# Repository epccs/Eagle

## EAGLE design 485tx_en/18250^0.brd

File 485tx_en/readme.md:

[485tx_en]

RS485 txcvr with fail-safe (e.g. 0V on A/B give HIGH on RO), thus TX can be used to enable media (A/B pair) driver. It does not work with industary standard based equipment.

[485tx_en]: https://github.com/epccs/Driver/tree/master/485tx_en

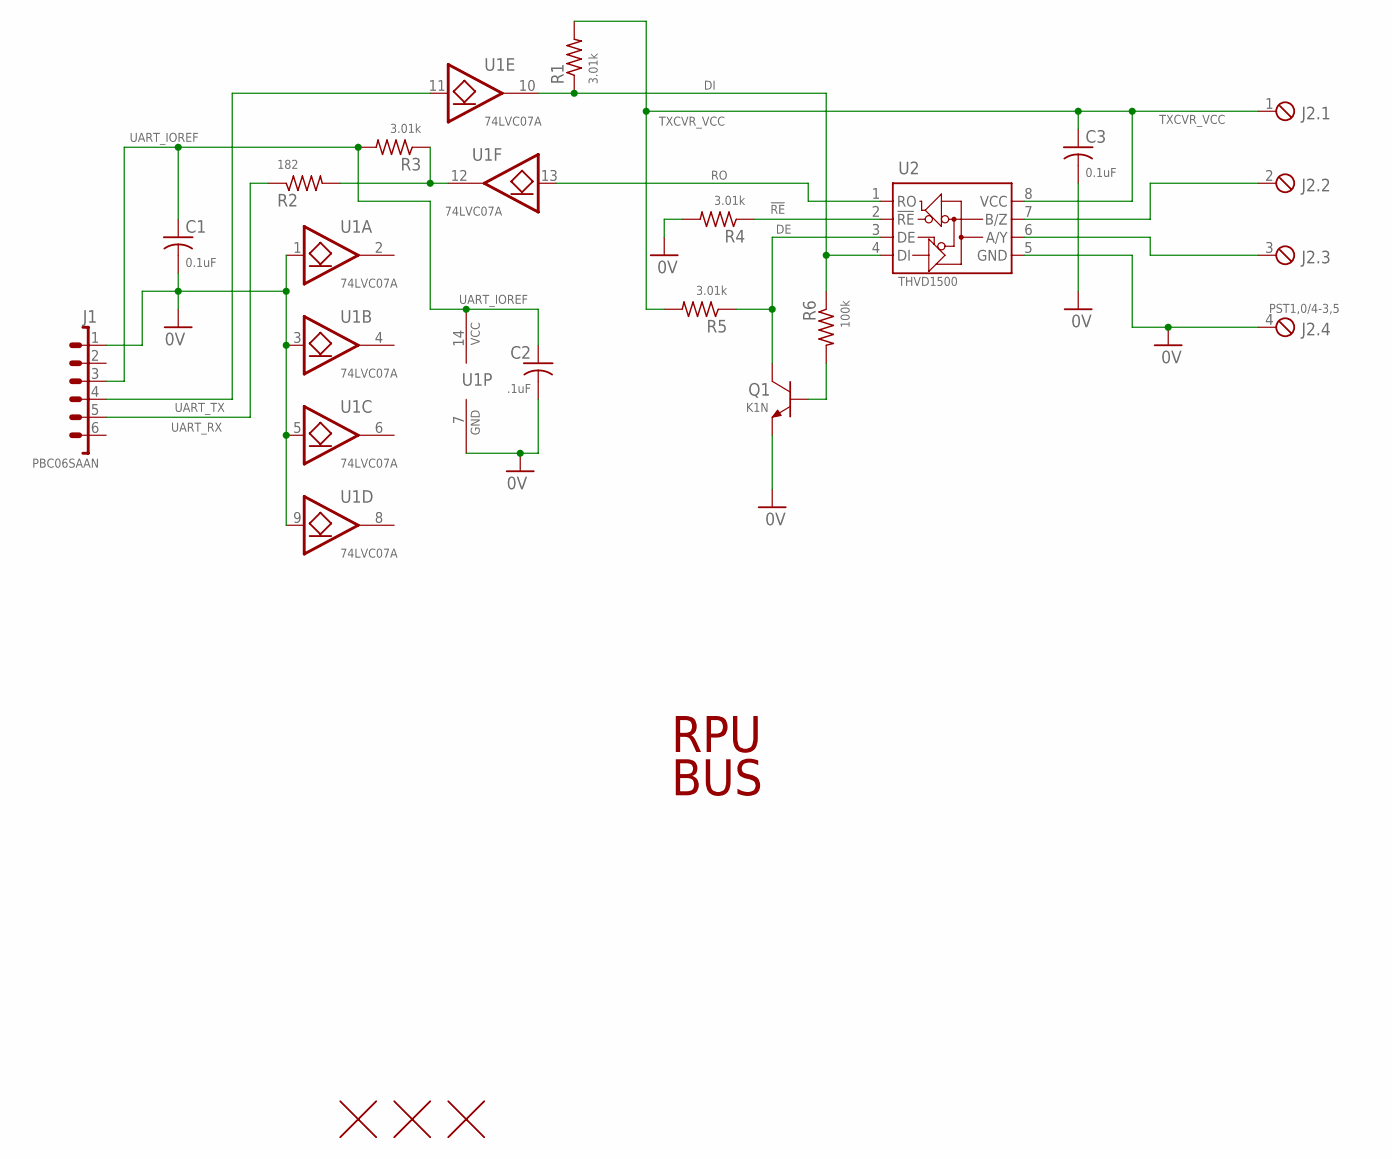
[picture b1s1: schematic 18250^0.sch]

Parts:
C1, C3: 0.1uF; C0603(1608)
C2: .1uF; C0603(1608)
J1: PBC06SAAN; 1X6
J2: PST1,0/4-3,5; MCV4
Q1: K1N; SOT23
R1, R3, R4, R5: 3.01k; C0805(2012)
R2: 182; C0805(2012)
R6: 100k; C0805(2012)
U1: 74LVC07A; 14SOIC
U2: THVD1500; SOIC8
U$2, U$3, U$4: FIDUCIAL1.27; FIDUCIAL-1.27

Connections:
0V: C1.2, C2.2, C3.2, J1.1, J2.4, Q1.E, R4.2, U1.1 (I), U1.3 (I), U1.5 (I), U1.7 (GND), U1.9 (I), U2.5 (GND)
!RE: R4.1, U2.2 (!RE)
A: J2.3, U2.6 (A/Y)
B: J2.2, U2.7 (B/Z)
DE: Q1.C, R5.1, U2.3 (DE)
DI: R1.1, R6.1, U1.10 (O), U2.4 (DI)
unnamed: R2.2, R3.1, U1.12 (O)
unnamed: Q1.B, R6.2
RO: U1.13 (I), U2.1 (RO)
TXCVR_VCC: C3.1, J2.1, R1.2, R5.2, U2.8 (VCC)
UART_IOREF: C1.1, C2.1, J1.3, R3.2, U1.14 (VCC)
UART_RX: J1.5, R2.1
UART_TX: J1.4, U1.11 (I)

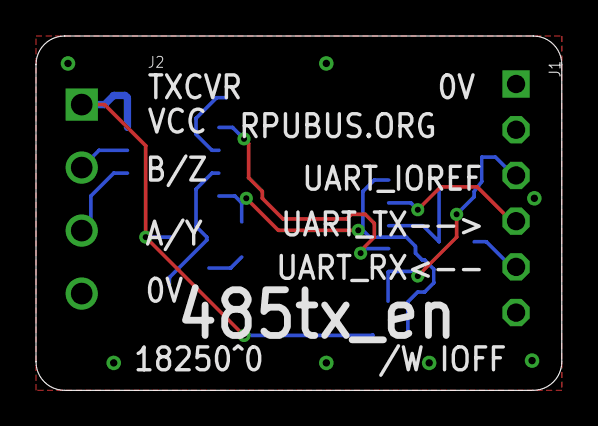
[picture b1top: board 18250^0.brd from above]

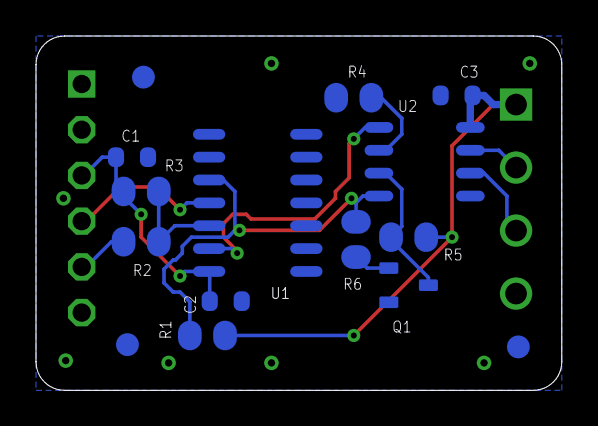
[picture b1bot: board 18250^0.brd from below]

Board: 2 copper layers, 29.2 x 19.7 mm, 17 parts (15 on the bottom side), 13 nets.

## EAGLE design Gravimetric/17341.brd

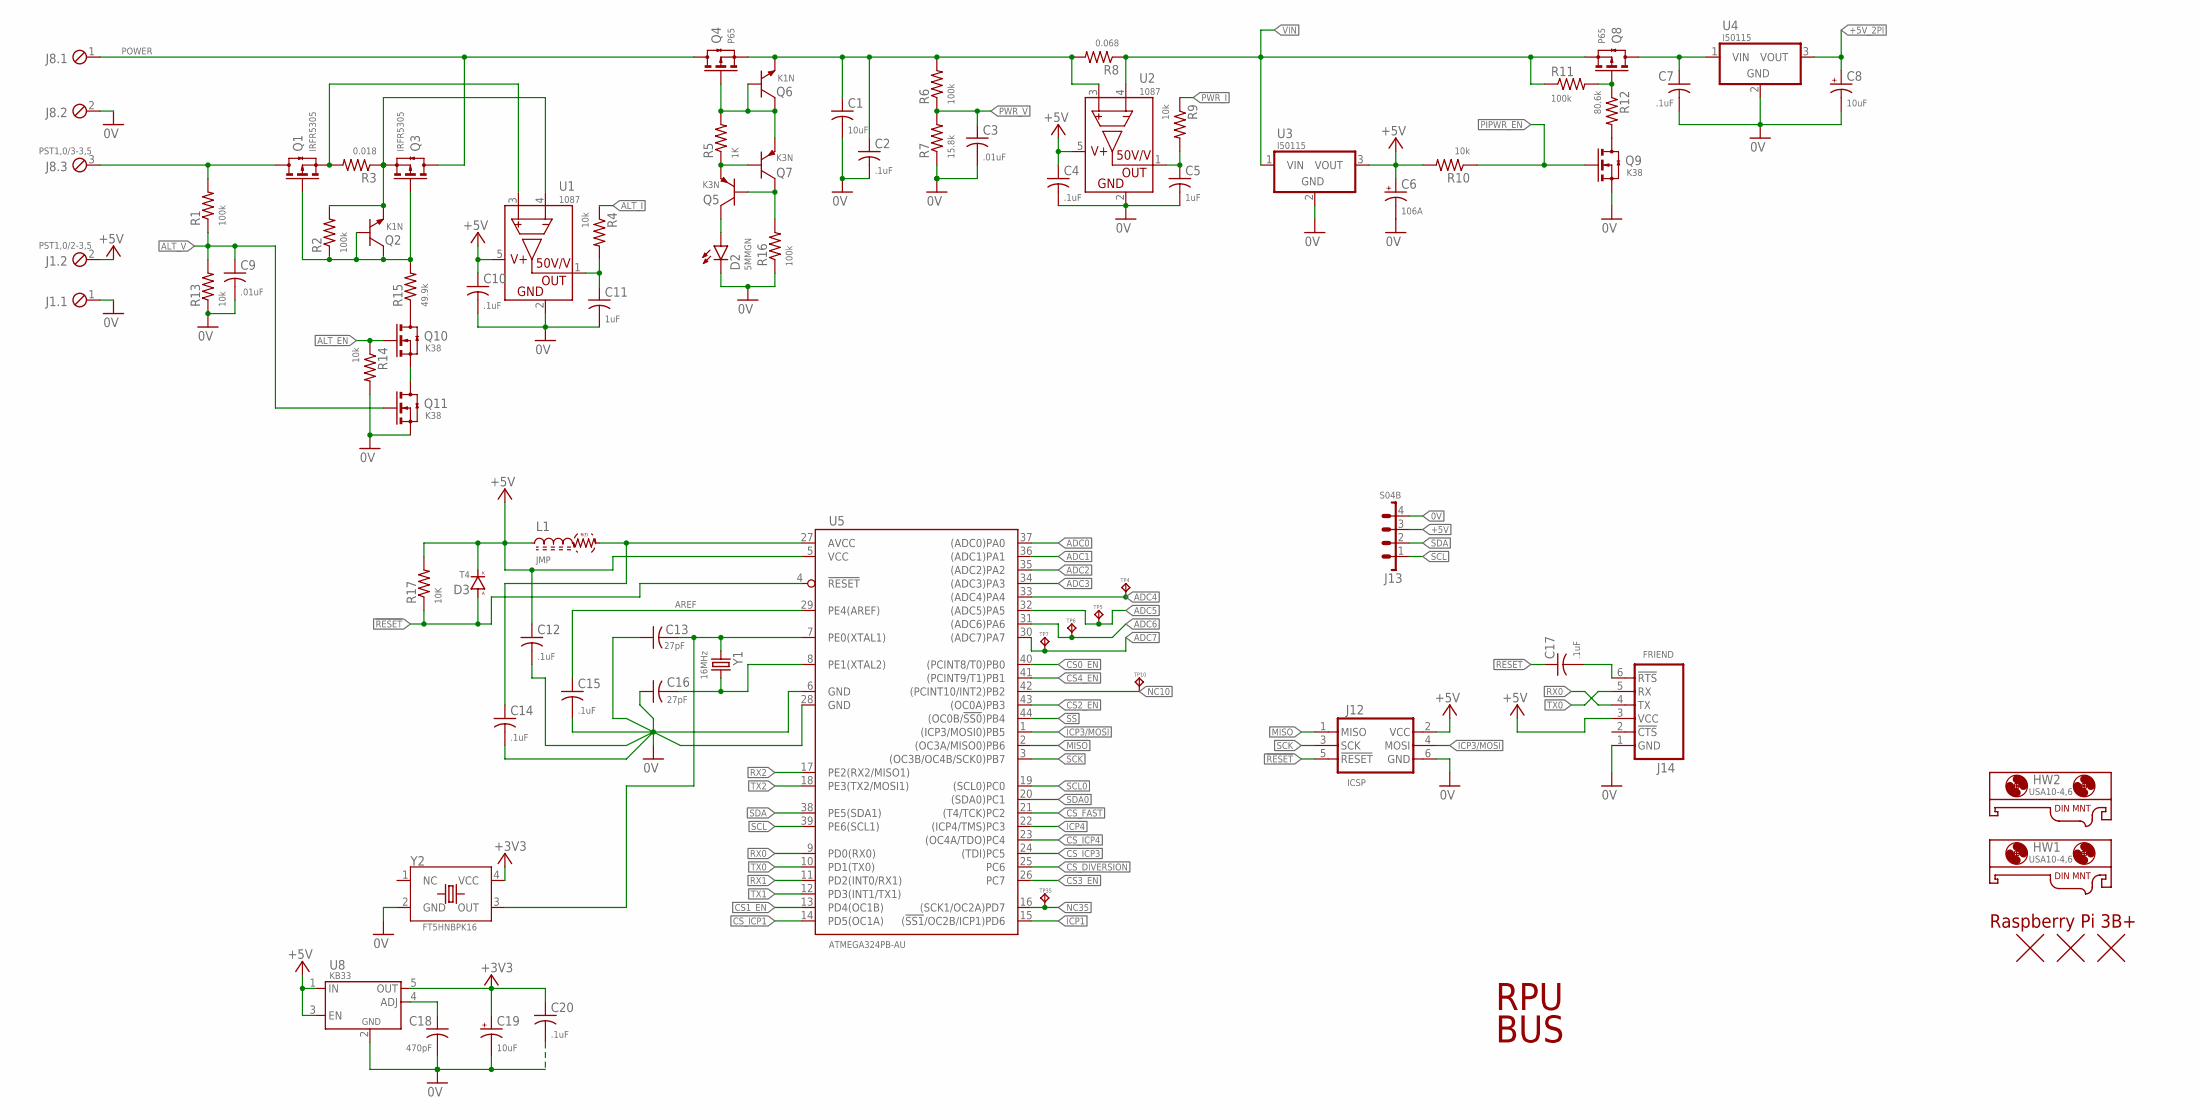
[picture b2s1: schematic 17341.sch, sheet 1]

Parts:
C1: 10uF; C1206(3216)
C2: .1uF; C0805(2012)
C3, C9: .01uF; C0603(1608)
C4, C7, C10, C12, C14, C15, C17, C20: .1uF; C0603(1608)
C5, C11: 1uF; C0805(2012)
C6: 106A; 3216
C8, C19: 10uF; 3216
C13, C16: 27pF; C0603(1608)
C18: 470pF; C0603(1608)
D2: 5MMGN; LED5MM
D3: T4; SOD123
HW1, HW2: USA10-4,6; USA10
J1: PST1,0/2-3,5; MCV2
J8: PST1,0/3-3,5; MCV3
J12: ICSP; ISP
J13: S04B; B04B
J14: FRIEND
L1: JMP; C0805(2012)
Q1, Q3: IRFR5305; DPAK
Q2, Q6: K1N; SOT23
Q4, Q8: P65; SOT23
Q5, Q7: K3N; SOT23
Q9, Q10, Q11: K38; SOT23
R1, R2, R6, R11, R16: 100k; C0805(2012)
R3: 0.018; C1210(3225)
R4, R9, R10, R13, R14: 10k; C0805(2012)
R5: 1K; C0805(2012)
R7: 15.8k; C0805(2012)
R8: 0.068; C1210(3225)
R12: 80.6k; C0805(2012)
R15: 49.9k; C0805(2012)
R17: 10K; C0805(2012)
TP4, TP5, TP6, TP7, TP10, TP35: TPPAD1-08; P1-08
U1, U2: 1087; SOT23-5
U3, U4: I50115; OKI-78SR-H
U5: ATMEGA324PB-AU; TQFP44
U8: KB33; SOT23-5,SOT25
U$1: R-PI3B+
U$2, U$3, U$4: FIDUCIAL1.27; FIDUCIAL-1.27
Y1: 16MHz; CSM-3X
Y2: FT5HNBPK16; CRYSTAL5X3.2MM

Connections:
0V: C1.2, C2.2, C3.2, C4.2, C5.2, C6.-, C7.2, C8.-, C9.2, C10.2, C11.2, C12.2, C13.1, C14.2, C15.2, C16.1, C18.2, C19.-, C20.2, D2.K, J1.1, J8.2, J12.6 (GND), J13.4, J14.1 (GND), Q9.2(S) (S), Q11.2(S) (S), R7.1, R13.1, R14.2, R16.1, U1.2 (GND), U2.2 (GND), U3.2 (GND), U4.2 (GND), U5.6 (GND), U5.28 (GND), U8.2 (GND), Y2.2 (GND); also elsewhere on the board
!RESET!: C17.1, D3.A, J12.5 (!RESET), R17.1, U5.4 (!RESET); also elsewhere on the board
!SS: U5.44 ((OC0B/!SS0!)PB4); also elsewhere on the board
+3V3: C19.+, C20.1, U8.5 (OUT), Y2.4 (VCC)
+5V: C4.1, C6.+, C10.1, C12.1, D3.C (K), J1.2, J12.2 (VCC), J13.3, J14.3 (VCC), L1.1, R10.2, R17.2, U1.5 (VCC), U2.5 (VCC), U3.3 (VOUT), U5.5 (VCC), U8.1 (IN), U8.3 (EN); also elsewhere on the board
+5V_2PI: C8.+, U4.3 (VOUT); also elsewhere on the board
ADC0: U5.37 ((ADC0)PA0); also elsewhere on the board
ADC1: U5.36 ((ADC1)PA1); also elsewhere on the board
ADC2: U5.35 ((ADC2)PA2); also elsewhere on the board
ADC3: U5.34 ((ADC3)PA3); also elsewhere on the board
ADC4: TP4.TP, U5.33 ((ADC4)PA4)
ADC5: TP5.TP, U5.32 ((ADC5)PA5)
ADC6: TP6.TP, U5.31 ((ADC6)PA6)
ADC7: TP7.TP, U5.30 ((ADC7)PA7)
ALT_EN: Q10.1(G) (G), R14.1; also elsewhere on the board
ALT_I: R4.1; also elsewhere on the board
ALT_V: C9.1, Q11.1(G) (G), R1.1, R13.2; also elsewhere on the board
AREF: C15.1, U5.29 (PE4(AREF))
CS0_EN: U5.40 ((PCINT8/T0)PB0); also elsewhere on the board
CS1_EN: U5.13 (PD4(OC1B)); also elsewhere on the board
CS2_EN: U5.43 ((OC0A)PB3); also elsewhere on the board
CS3_EN: U5.26 (PC7); also elsewhere on the board
CS4_EN: U5.41 ((PCINT9/T1)PB1); also elsewhere on the board
CS_DIVERSION: U5.25 (PC6); also elsewhere on the board
CS_FAST: U5.21 ((T4/TCK)PC2); also elsewhere on the board
CS_ICP1: U5.14 (PD5(OC1A)); also elsewhere on the board
CS_ICP3: U5.24 ((TDI)PC5); also elsewhere on the board
CS_ICP4: U5.23 ((OC4A/TDO)PC4); also elsewhere on the board
ICP1: U5.15 ((!SS1!/OC2B/ICP1)PD6); also elsewhere on the board
ICP3/MOSI: J12.4 (MOSI), U5.1 ((ICP3/MOSI0)PB5); also elsewhere on the board
ICP4: U5.22 ((ICP4/TMS)PC3); also elsewhere on the board
MISO: J12.1 (MISO), U5.2 ((OC3A/MISO0)PB6); also elsewhere on the board
unnamed: Q8.1(G) (G), R11.2, R12.1
unnamed: Q9.3(D) (D), R12.2
unnamed: Q5.B, Q7.C, R16.2
unnamed: Q4.1(G) (G), Q6.B, Q6.C, Q7.E, R5.2
unnamed: D2.A, Q5.C
unnamed: C5.1, R9.2, U2.1 (OUT)
unnamed: Q5.E, Q7.B, R5.1
unnamed: J8.3, Q1.SINK (D), R1.2
unnamed: Q2.E, Q3.3 (S), R2.2, R3.1, U1.4 (S-)
unnamed: Q1.1 (G), Q2.B, Q2.C, Q3.1 (G), R2.1, R15.2
unnamed: Q10.3(D) (D), R15.1
unnamed: C17.2, J14.6 (!RTS)
unnamed: C11.1, R4.2, U1.1 (OUT)
unnamed: Q1.3 (S), R3.2, U1.3 (S+)
unnamed: C16.2, U5.8 (PE1(XTAL2)), Y1.2
unnamed: C18.1, U8.4 (ADJ)
unnamed: C14.1, L1.2, U5.27 (AVCC)
unnamed: C13.2, U5.7 (PE0(XTAL1)), Y1.1, Y2.3 (OUT)
unnamed: Q10.2(S) (S), Q11.3(D) (D)
NC10: TP10.TP, U5.42 ((PCINT10/INT2)PB2)
NC35: TP35.TP, U5.16 ((SCK1/OC2A)PD7)
PIPWR_EN: Q9.1(G) (G), R10.1; also elsewhere on the board
POWER: J8.1, Q3.SINK (D), Q4.3(D) (D)
PWR_I: R9.1; also elsewhere on the board
PWR_V: C3.1, R6.1, R7.2; also elsewhere on the board
RX0: J14.4 (TX), U5.9 (PD0(RX0)); also elsewhere on the board
RX1: U5.11 (PD2(INT0/RX1)); also elsewhere on the board
RX2: U5.17 (PE2(RX2/MISO1)); also elsewhere on the board
SCK: J12.3 (SCK), U5.3 ((OC3B/OC4B/SCK0)PB7); also elsewhere on the board
SCL: J13.1, U5.39 (PE6(SCL1))
SCL0: U5.19 ((SCL0)PC0); also elsewhere on the board
SDA: J13.2, U5.38 (PE5(SDA1))
SDA0: U5.20 ((SDA0)PC1); also elsewhere on the board
SHLD_VIN: C7.1, Q8.3(D) (D), U4.1 (VIN)
TX0: J14.5 (RX), U5.10 (PD1(TX0)); also elsewhere on the board
TX1: U5.12 (PD3(INT1/TX1)); also elsewhere on the board
TX2: U5.18 (PE3(TX2/MOSI1)); also elsewhere on the board
VIN: Q8.2(S) (S), R8.1, R11.1, U2.4 (S-), U3.1 (VIN); also elsewhere on the board
VIN_S: C1.1, C2.1, Q4.2(S) (S), Q6.E, R6.2, R8.2, U2.3 (S+)

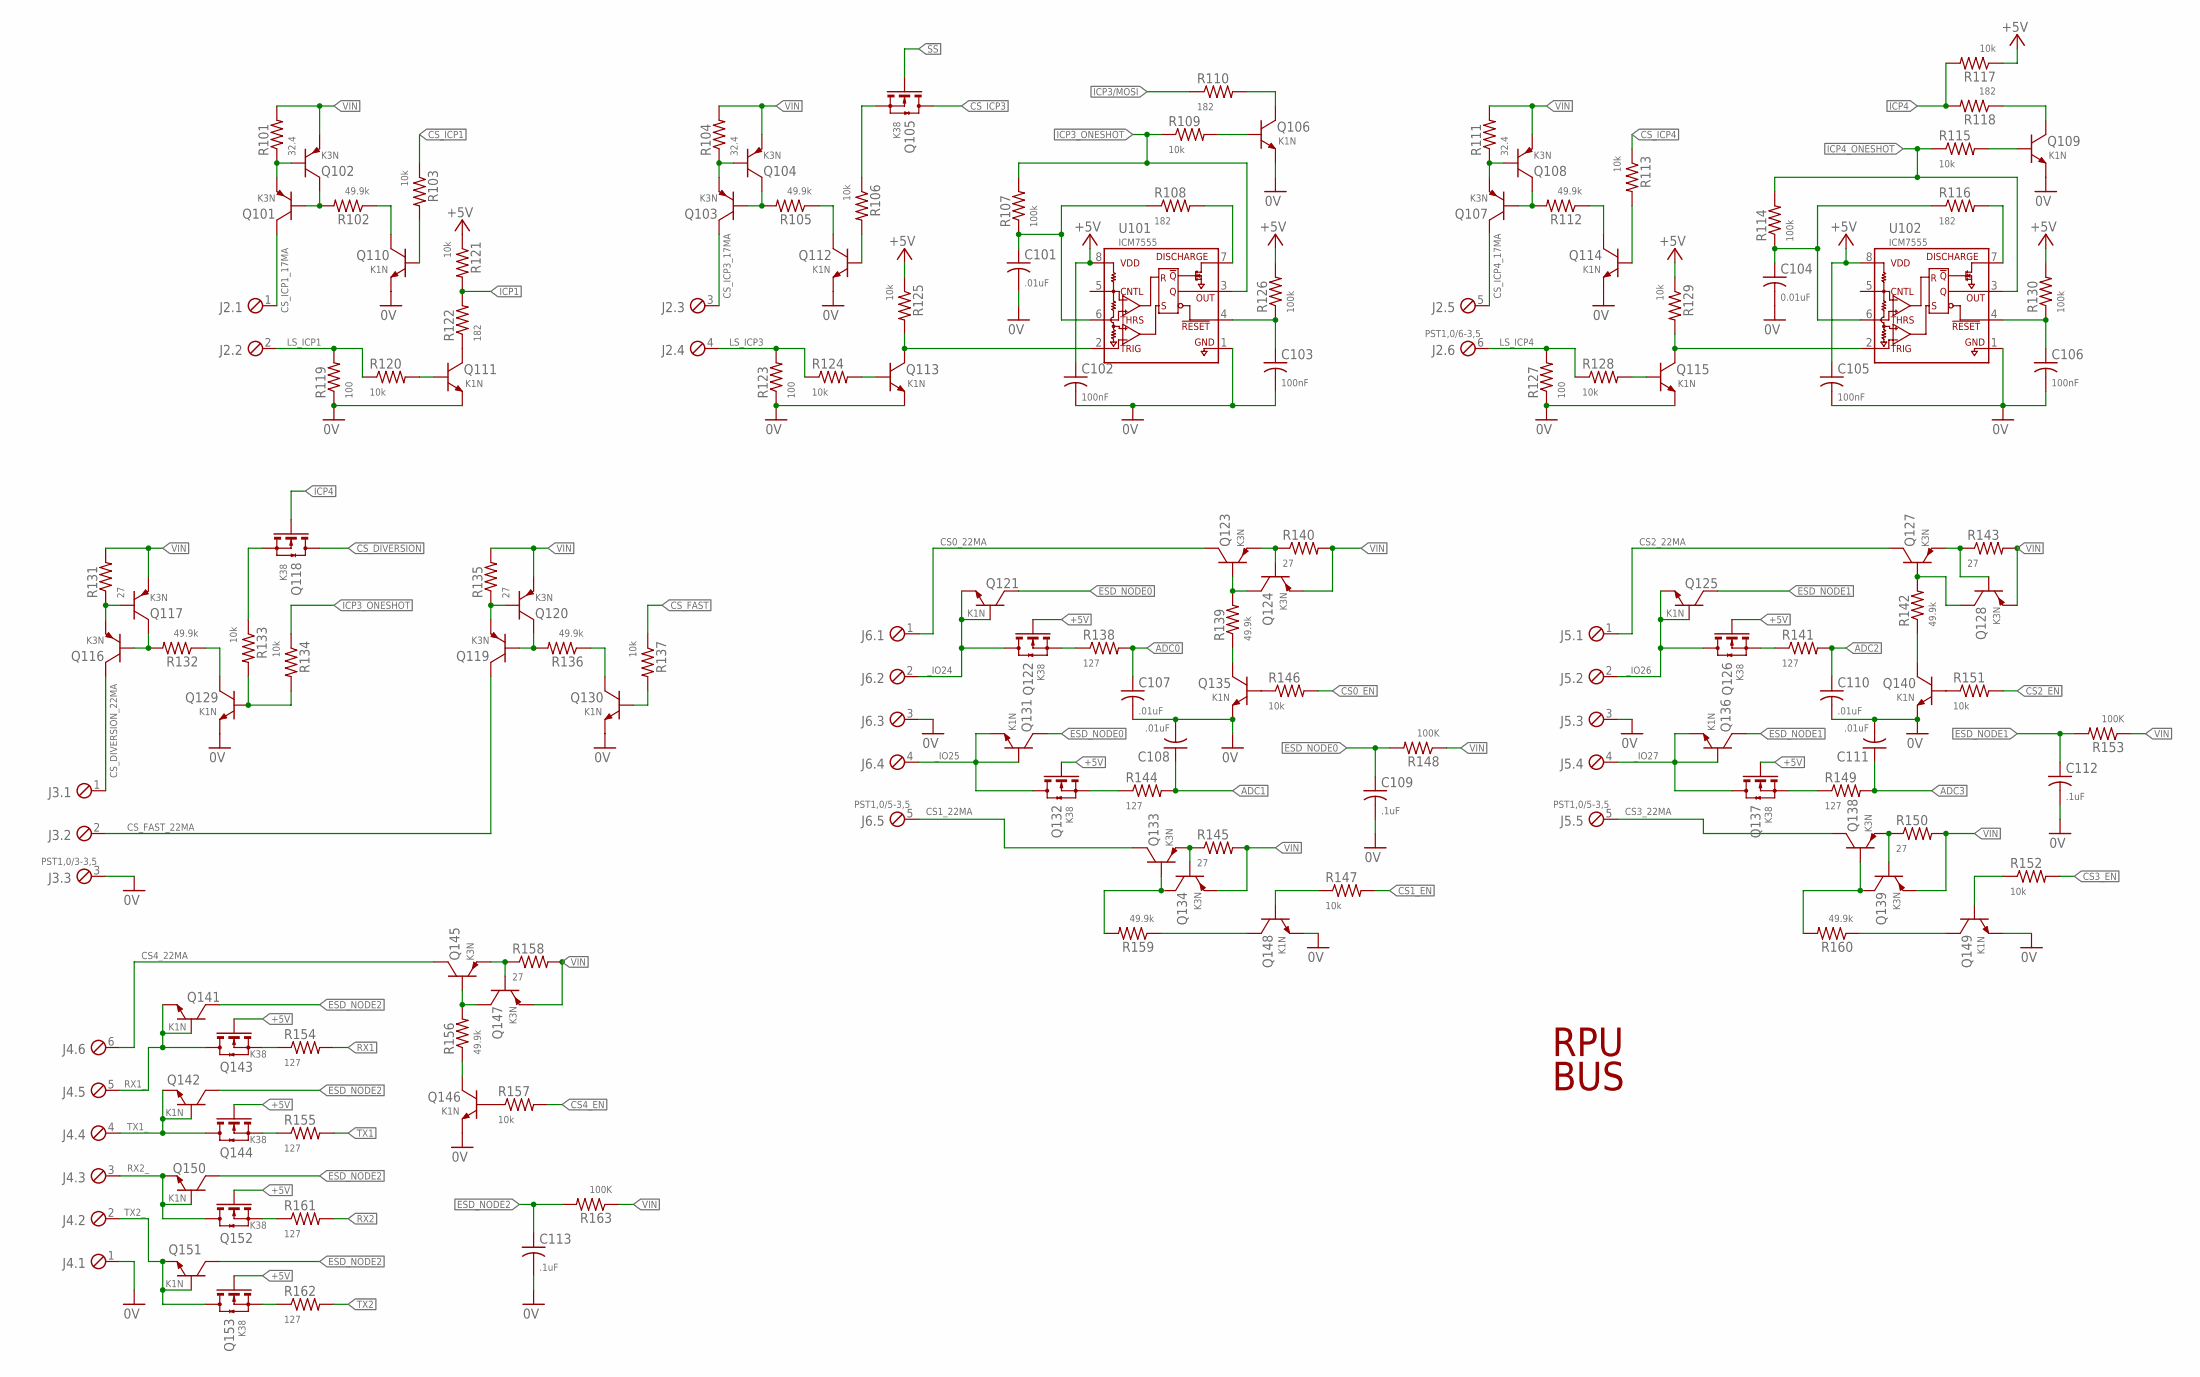
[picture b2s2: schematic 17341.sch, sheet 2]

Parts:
C101: .01uF; C0805(2012)
C102, C103, C105, C106: 100nF; C0603(1608)
C104: 0.01uF; C0805(2012)
C107, C108, C110, C111: .01uF; C0603(1608)
C109, C112, C113: .1uF; C0603(1608)
J2: PST1,0/6-3,5; MCV6
J3: PST1,0/3-3,5; MCV3
J4: MCV6
J5, J6: PST1,0/5-3,5; MCV5
Q101, Q102, Q103, Q104, Q107, Q108, Q116, Q117, Q119, Q120, Q123, Q124, Q127, Q128, Q133, Q134, Q138, Q139, Q145, Q147: K3N; SOT23
Q105, Q118, Q122, Q126, Q132, Q137, Q143, Q144, Q152, Q153: K38; SOT23
Q106, Q109, Q110, Q111, Q112, Q113, Q114, Q115, Q121, Q125, Q129, Q130, Q131, Q135, Q136, Q140, Q141, Q142, Q146, Q148, Q149, Q150, Q151: K1N; SOT23
R101, R104, R111: 32.4; C0805(2012)
R102, R105, R112, R132, R136, R139, R142, R156, R159, R160: 49.9k; C0805(2012)
R103, R106, R109, R113, R115, R117, R120, R121, R124, R125, R128, R129, R133, R134, R137, R146, R147, R151, R152, R157: 10k; C0805(2012)
R107, R114, R126, R130: 100k; C0805(2012)
R108, R110, R116, R118, R122: 182; C0805(2012)
R119, R123, R127: 100; C0805(2012)
R131, R135, R140, R143, R145, R150, R158: 27; C0805(2012)
R138, R141, R144, R149, R154, R155, R161, R162: 127; C0805(2012)
R148, R153, R163: 100K; C0805(2012)
U101, U102: ICM7555; SOIC8

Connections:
0V: C101.2, C102.2, C103.2, C104.2, C105.2, C106.2, C107.2, C108.2, C109.2, C110.2, C111.2, C112.2, C113.2, J3.3, J4.1, J5.3, J6.3, Q106.E, Q109.E, Q110.E, Q111.E, Q112.E, Q113.E, Q114.E, Q115.E, Q129.E, Q130.E, Q135.E, Q140.E, Q146.E, Q148.E, Q149.E, R119.1, R123.1, R127.1, U101.1 (GND), U102.1 (GND); also elsewhere on the board
!SS: Q105.1(G) (G); also elsewhere on the board
+5V: C102.1, C105.1, Q122.1(G) (G), Q126.1(G) (G), Q132.1(G) (G), Q137.1(G) (G), Q143.1(G) (G), Q144.1(G) (G), Q152.1(G) (G), Q153.1(G) (G), R117.1, R121.1, R125.1, R126.2, R129.1, R130.2, U101.8 (VDD), U102.8 (VDD); also elsewhere on the board
ADC0: C107.1, R138.2; also elsewhere on the board
ADC1: C108.1, R144.2; also elsewhere on the board
ADC2: C110.1, R141.2; also elsewhere on the board
ADC3: C111.1, R149.2; also elsewhere on the board
CS0_22MA: J6.1, Q123.C
CS0_EN: R146.2; also elsewhere on the board
CS1_22MA: J6.5, Q133.C
CS1_EN: R147.2; also elsewhere on the board
CS2_22MA: J5.1, Q127.C
CS2_EN: R151.2; also elsewhere on the board
CS3_22MA: J5.5, Q138.C
CS3_EN: R152.2; also elsewhere on the board
CS4_22MA: J4.6, Q145.C
CS4_EN: R157.2; also elsewhere on the board
CS_DIVERSION: Q118.3(D) (D); also elsewhere on the board
CS_DIVERSION_22MA: J3.1, Q116.C
CS_FAST: R137.1; also elsewhere on the board
CS_FAST_22MA: J3.2, Q119.C
CS_ICP1: R103.1; also elsewhere on the board
CS_ICP1_17MA: J2.1, Q101.C
CS_ICP3: Q105.3(D) (D); also elsewhere on the board
CS_ICP3_17MA: J2.3, Q103.C
CS_ICP4: R113.1; also elsewhere on the board
CS_ICP4_17MA: J2.5, Q107.C
ESD_NODE0: C109.1, Q121.C, Q131.C, R148.2
ESD_NODE1: C112.1, Q125.C, Q136.C, R153.2
ESD_NODE2: C113.1, Q141.C, Q142.C, Q150.C, Q151.C, R163.2
ICP1: R121.2, R122.2; also elsewhere on the board
ICP1__: Q111.B, R120.2
ICP3/MOSI: R110.1; also elsewhere on the board
ICP3_ONESHOT: R107.2, R109.1, R134.1, U101.3 (OUT)
ICP3_TIMING_RAMP: C101.1, R107.1, R108.1, U101.6 (THRS)
ICP3__: Q113.B, R124.2
ICP4: Q118.1(G) (G), R117.2, R118.2; also elsewhere on the board
ICP4_ONESHOT: R114.2, R115.1, U102.3 (OUT)
ICP4_TIMING_RAMP: C104.1, R114.1, R116.1, U102.6 (THRS)
ICP4__: Q115.B, R128.2
LS_ICP1: J2.2, R119.2, R120.1
LS_ICP3: J2.4, R123.2, R124.1
LS_ICP4: J2.6, R127.2, R128.1
unnamed: Q127.E, Q128.B, R143.1
unnamed: Q110.B, R103.2
unnamed: Q127.B, Q128.C, R142.2
unnamed: Q103.E, Q104.B, R104.1
unnamed: Q138.E, Q139.B, R150.1
unnamed: Q132.2(S) (S), R144.1
unnamed: Q122.2(S) (S), R138.1
unnamed: Q138.B, Q139.C, R160.2
unnamed: Q103.B, Q104.C, R105.2
unnamed: Q115.C, R129.2, U102.2 (TRIG)
unnamed: Q148.C, R159.1
unnamed: Q123.E, Q124.B, R140.1
unnamed: Q135.C, R139.1
unnamed: Q112.B, R106.2
unnamed: Q123.B, Q124.C, R139.2
unnamed: Q107.E, Q108.B, R111.1
unnamed: Q107.B, Q108.C, R112.2
unnamed: Q109.B, R115.2
unnamed: Q133.E, Q134.B, R145.1
unnamed: Q133.B, Q134.C, R159.2
unnamed: Q114.B, R113.2
unnamed: Q148.B, R147.1
unnamed: Q135.B, R146.1
unnamed: Q149.C, R160.1
unnamed: Q110.C, R102.1
unnamed: Q112.C, R105.1
unnamed: Q114.C, R112.1
unnamed: Q105.2(S) (S), R106.1
unnamed: Q113.C, R125.2, U101.2 (TRIG)
unnamed: Q109.C, R118.1
unnamed: Q116.E, Q117.B, R131.1
unnamed: R116.2, U102.7 (DISCHARGE)
unnamed: C106.1, R130.1, U102.4 (!RESET)
unnamed: Q106.B, R109.2
unnamed: R108.2, U101.7 (DISCHARGE)
unnamed: Q106.C, R110.2
unnamed: C103.1, R126.1, U101.4 (!RESET)
unnamed: Q116.B, Q117.C, R132.2
unnamed: Q129.B, R133.2, R134.2
unnamed: Q129.C, R132.1
unnamed: Q118.2(S) (S), R133.1
unnamed: Q119.E, Q120.B, R135.1
unnamed: Q119.B, Q120.C, R136.2
unnamed: Q130.B, R137.2
unnamed: Q130.C, R136.1
unnamed: Q140.C, R142.1
unnamed: Q137.2(S) (S), R149.1
unnamed: Q126.2(S) (S), R141.1
unnamed: Q149.B, R152.1
unnamed: Q140.B, R151.1
unnamed: Q145.E, Q147.B, R158.1
unnamed: Q145.B, Q147.C, R156.2
unnamed: Q153.2(S) (S), R162.1
unnamed: Q152.2(S) (S), R161.1
unnamed: Q146.C, R156.1
unnamed: Q144.2(S) (S), R155.1
unnamed: Q143.2(S) (S), R154.1
unnamed: Q146.B, R157.1
unnamed: Q111.C, R122.1
unnamed: Q101.E, Q102.B, R101.1
unnamed: Q101.B, Q102.C, R102.2
RX1: R154.2; also elsewhere on the board
RX1_: J4.5, Q141.B, Q141.E, Q143.3(D) (D)
RX2: R161.2; also elsewhere on the board
RX2_: J4.3, Q150.B, Q150.E, Q152.3(D) (D)
TX1: R155.2; also elsewhere on the board
TX1_: J4.4, Q142.B, Q142.E, Q144.3(D) (D)
TX2: R162.2; also elsewhere on the board
TX2_: J4.2, Q151.B, Q151.E, Q153.3(D) (D)
VIN: Q102.E, Q104.E, Q108.E, Q117.E, Q120.E, Q124.E, Q128.E, Q134.E, Q139.E, Q147.E, R101.2, R104.2, R111.2, R131.2, R135.2, R140.2, R143.2, R145.2, R148.1, R150.2, R153.1, R158.2, R163.1; also elsewhere on the board
_IO24: J6.2, Q121.B, Q121.E, Q122.3(D) (D)
_IO25: J6.4, Q131.B, Q131.E, Q132.3(D) (D)
_IO26: J5.2, Q125.B, Q125.E, Q126.3(D) (D)
_IO27: J5.4, Q136.B, Q136.E, Q137.3(D) (D)

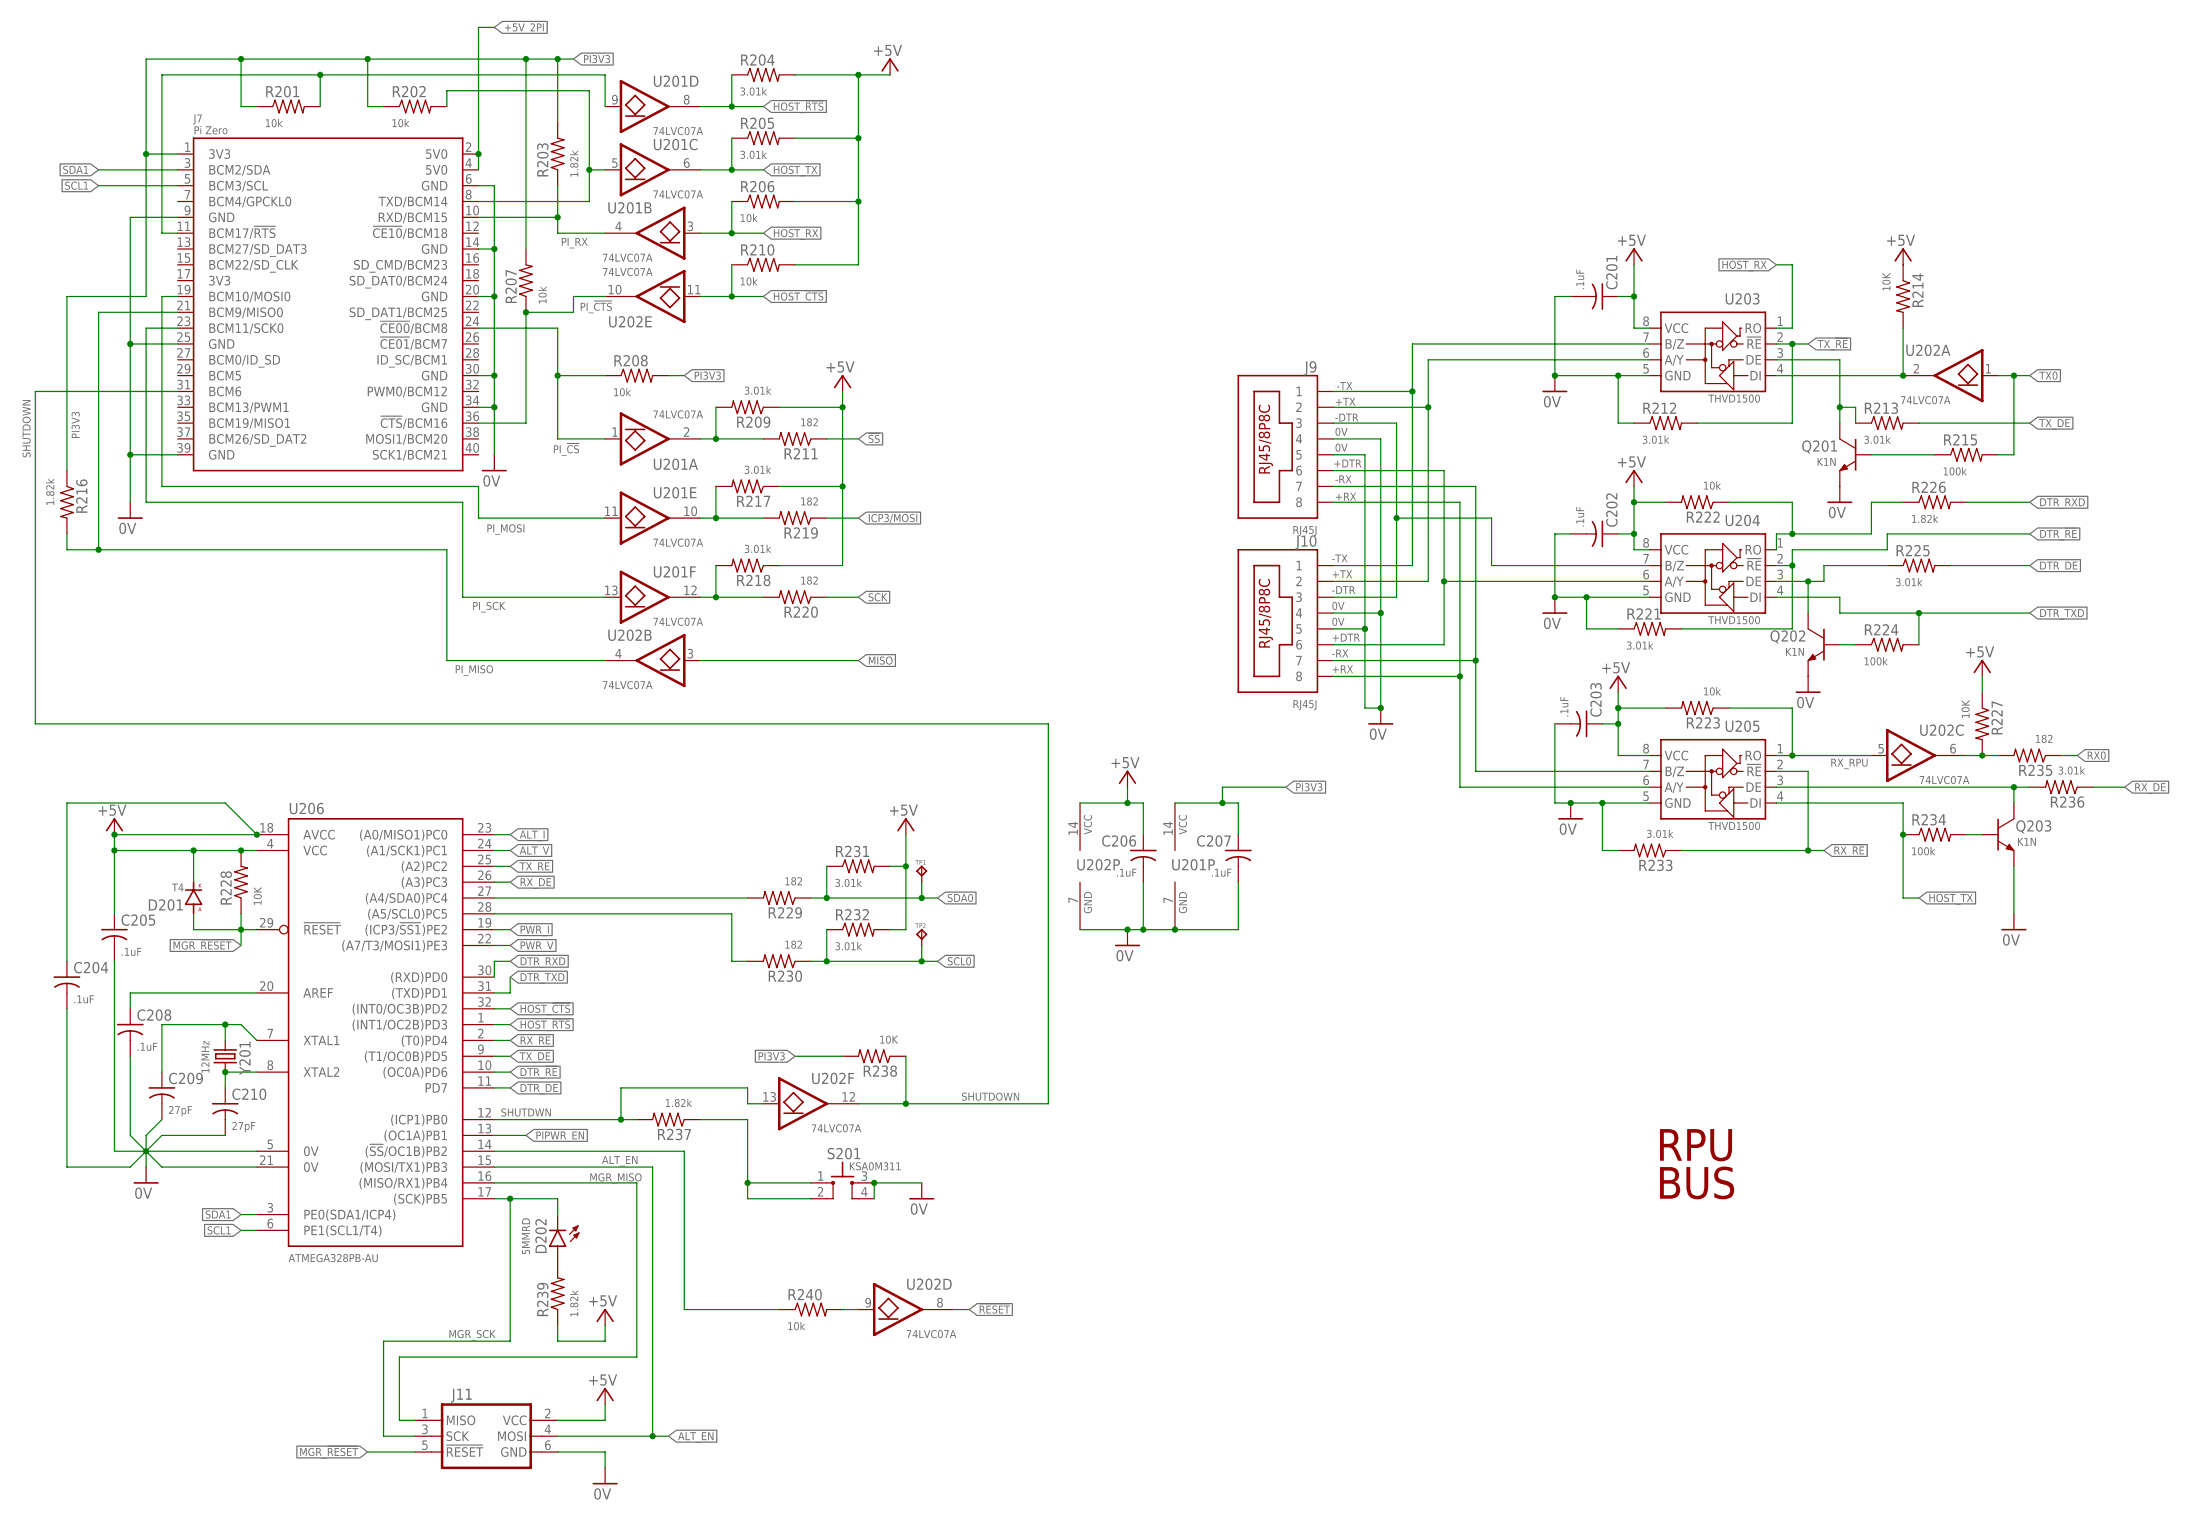
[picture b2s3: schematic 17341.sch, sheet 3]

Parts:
C201, C202, C203, C204, C205, C206, C207, C208: .1uF; C0603(1608)
C209, C210: 27pF; C0603(1608)
D201: T4; SOD123
D202: 5MMRD; LED5MM
J7: Pi Zero; RASPI_ZERO_V40PIN
J9, J10: RJ45J; RJ45-8HZT
J11: ISP-SPIPTH; ISP
Q201, Q202, Q203: K1N; SOT23
R201, R202, R206, R207, R208, R210, R222, R223, R240: 10k; C0805(2012)
R203, R216, R226, R237, R239: 1.82k; C0805(2012)
R204, R205, R209, R212, R213, R217, R218, R221, R225, R231, R232, R233, R236: 3.01k; C0805(2012)
R211, R219, R220, R229, R230, R235: 182; C0805(2012)
R214, R227, R228, R238: 10K; C0805(2012)
R215, R224, R234: 100k; C0805(2012)
S201: KSA0M311; 0M311
TP1, TP2: TPPAD1-08; P1-08
U201, U202: 74LVC07A; 14SOIC
U203, U204, U205: THVD1500; SOIC8
U206: ATMEGA328PB-AU; TQFP32-08
Y201: 12MHz; CSM-3X

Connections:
0V: C201.2, C202.2, C203.2, C204.2, C205.2, C206.2, C207.2, C208.2, C209.2, C210.2, J7.6 (GND), J7.9 (GND), J7.14 (GND), J7.20 (GND), J7.25 (GND), J7.30 (GND), J7.34 (GND), J7.39 (GND), J9.4, J9.5, J10.4, J10.5, J11.6 (GND), Q201.E, Q202.E, Q203.E, R212.1, R221.1, R233.2, S201.3, S201.4, U201.7 (GND), U202.7 (GND), U203.5 (GND), U204.5 (GND), U205.5 (GND), U206.5 (0V), U206.21 (0V); also elsewhere on the board
!RESET!: U202.8 (O); also elsewhere on the board
!SS: R211.1; also elsewhere on the board
+5V: C201.1, C202.1, C203.1, C204.1, C205.1, C206.1, D201.C (K), J11.2 (VCC), R204.2, R205.2, R206.2, R209.1, R210.2, R214.1, R217.1, R218.1, R222.2, R223.2, R227.1, R228.2, R231.2, R232.2, R239.1, U202.14 (VCC), U203.8 (VCC), U204.8 (VCC), U205.8 (VCC), U206.4 (VCC), U206.18 (AVCC); also elsewhere on the board
+5V_2PI: J7.2 (5V0), J7.4 (5V0); also elsewhere on the board
+DTR: J9.6, J10.6, U204.6 (A/Y)
+RX: J9.8, J10.8, U205.6 (A/Y)
+TX: J9.2, J10.2, U203.6 (A/Y)
-DTR: J9.3, J10.3, U204.7 (B/Z)
-RX: J9.7, J10.7, U205.7 (B/Z)
-TX: J9.1, J10.1, U203.7 (B/Z)
ALT_EN: J11.4 (MOSI), U206.15 ((MOSI/TX1)PB3); also elsewhere on the board
ALT_I: U206.23 ((A0/MISO1)PC0); also elsewhere on the board
ALT_V: U206.24 ((A1/SCK1)PC1); also elsewhere on the board
DTR_!RE: R221.2, U204.2 (!RE), U206.10 ((OC0A)PD6)
DTR_DE: R225.2, U206.11 (PD7)
DTR_RXD: R226.2, U206.30 ((RXD)PD0)
DTR_TXD: R224.2, U204.4 (DI), U206.31 ((TXD)PD1)
HOST_!CTS: R210.1, U202.11 (I), U206.32 ((INT0/OC3B)PD2)
HOST_!RTS: R204.1, U201.8 (O), U206.1 ((INT1/OC2B)PD3)
HOST_RX: R206.1, U201.3 (I), U203.1 (RO)
HOST_TX: R205.1, R234.1, U201.6 (O), U205.4 (DI)
ICP3/MOSI: R219.1; also elsewhere on the board
MGR_!RESET: D201.A, J11.5 (!RESET), R228.1, U206.29 (!RESET)
MGR_!SS!: R240.1, U206.14 ((!SS!/OC1B)PB2)
MGR_AREF: C208.1, U206.20 (AREF)
MGR_MISO: J11.1 (MISO), U206.16 ((MISO/RX1)PB4)
MGR_SCK: D202.K, J11.3 (SCK), U206.17 ((SCK)PB5)
MISO: U202.3 (I); also elsewhere on the board
unnamed: R227.2, R235.2, U202.6 (O)
unnamed: Q201.B, R215.1
unnamed: Q201.C, R213.1, U203.3 (DE)
unnamed: R222.1, R226.1, U204.1 (RO)
unnamed: Q202.C, R225.1, U204.3 (DE)
unnamed: Q202.B, R224.1
unnamed: Q203.B, R234.2
unnamed: D202.A, R239.2
unnamed: Q203.C, R236.2, U205.3 (DE)
unnamed: R240.2, U202.9 (I)
unnamed: J7.8 (TXD/BCM14), R202.2, U201.5 (I)
unnamed: J7.11 (BCM17/!RTS!), R201.2, U201.9 (I)
unnamed: R218.2, R220.2, U201.12 (O)
unnamed: R217.2, R219.2, U201.10 (O)
unnamed: R237.1, S201.1, S201.2
unnamed: R229.2, U206.27 ((A4/SDA0)PC4)
unnamed: R230.2, U206.28 ((A5/SCL0)PC5)
unnamed: R209.2, R211.2, U201.2 (O)
PI3V3: C207.1, J7.1 (3V3), R201.1, R202.1, R203.2, R207.2, R208.2, R216.1, R238.2, U201.14 (VCC)
PIPWR_EN: U206.13 ((OC1A)PB1); also elsewhere on the board
PI_!CS: J7.24 (!CE00!/BCM8), R208.1, U201.1 (I)
PI_!CTS: J7.36 (!CTS!/BCM16), R207.1, U202.10 (O)
PI_MISO: J7.21 (BCM9/MISO0), R216.2, U202.4 (O)
PI_MOSI: J7.19 (BCM10/MOSI0), U201.11 (I)
PI_RX: J7.10 (RXD/BCM15), R203.1, U201.4 (O)
PI_SCK: J7.23 (BCM11/SCK0), U201.13 (I)
PWR_I: U206.19 ((ICP3/!SS1!)PE2); also elsewhere on the board
PWR_V: U206.22 ((A7/T3/MOSI1)PE3); also elsewhere on the board
RX0: R235.1; also elsewhere on the board
RX_!RE: R233.1, U205.2 (!RE), U206.2 ((T0)PD4)
RX_DE: R236.1, U206.26 ((A3)PC3)
RX_RPU: R223.1, U202.5 (I), U205.1 (RO)
SCK: R220.1; also elsewhere on the board
SCL0: R230.1, R232.1, TP2.TP; also elsewhere on the board
SCL1: J7.5 (BCM3/SCL), U206.6 (PE1(SCL1/T4))
SDA0: R229.1, R231.1, TP1.TP; also elsewhere on the board
SDA1: J7.3 (BCM2/SDA), U206.3 (PE0(SDA1/ICP4))
SHUTDOWN: J7.31 (BCM6), R238.1, U202.12 (O)
SHUTDWN: R237.2, U202.13 (I), U206.12 ((ICP1)PB0)
TX0: R215.2, U202.1 (I); also elsewhere on the board
TX_!RE: R212.2, U203.2 (!RE), U206.25 ((A2)PC2)
TX_DE: R213.2, U206.9 ((T1/OC0B)PD5)
TX_RPU: R214.2, U202.2 (O), U203.4 (DI)
XTAL1: C209.1, U206.7 (XTAL1), Y201.1
XTAL2: C210.1, U206.8 (XTAL2), Y201.2

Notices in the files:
parts and their libraries:
C-C: Copyright (C) 2013 Ronald Steven Sutherland
Released under the Creative Commons
Attribution Share-Alike 3.0 License
http://creativecommons.org/licenses/by-sa/3.0
R-C: under the terms of the GNU Free Documentation License, Version 1.2 or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
H-Frames: Copyright (C) 2018 Ronald Sutherland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
